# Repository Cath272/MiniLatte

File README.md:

# MiniLatte

## Introduction
MiniLatte is a Mini Pc made using the LattePanda Mu compute module

## General description
The device is a x86 desktop comuter with lots of IO ports like USB, PCIe, Ethernet and more. 

## Problems
Esp32 and GL3224 do not enumerate sometimes
The headphone jack is not correctly wired and i did not figure out how to fix it yet

### Block diagram

## Hardware Design
### LattePanda Mu 
The LattePanda Mu is a compute module with rich IO with up to 9 PCIe slots, lots of usb, gpio and much more.
The module is Avaliable with 8 or 16gb of LPDDR5 ram, and an Intel N100 or Intel N305 CPU, the module uses a SODIMM DDR4 slot to connect to the carrier pcb

## ICs 
The board uses a lot of ics, so to avoid a long section about ics you can find the complete list of ICs in an the BOM generator in KiCad
All parts that are not generic (Like caps and resistors) are directly imported from LCSC so they also have an LCSC id 
Please read the warning on the IT8851-128 if you want to build the board.

Some of the chips are not available on components sourcing sites like DigiKey or LCSC but can be easliy found of Aliexpress.
Some notable Ics used by the board:

### VL822-Q7
USB 3.2 Gen 2 USB Hub 10Gbps with 4 downstream ports, used to increase the number of usb from 2 to 8

### GL3224ONY
USB 3.2 Gen 1 to dual Sd card controller, used to have 2 sd cards slots on the pcb

### IT8851FN-128
Usb Type C DP alt mode Controller, used for having a usb C port with Displayport output, the chip is a bit hard to get but you can find it on Aliexpress if you ask some BOM sellers. The chip also needs to be flashed so ask the Lattepanda team for the flashing firmware.
The chip variant needs to be "IT8851-128" EXACTLY, other variants do not work.  

### TPS51275

Main Power Ic, used for DC-DC from 20v to 3.3v and 5v

### VL162
USB Type-C 2:4 differential channels mux switch and integrated CC logic function for USB 3.1 type-C application. Needed for the type C ports to work both ways.

### RTL8125BG
PCIe to 2.5Gbps Ethernet controller

## Schematic
[Schematic](PCB/MiniLatte.pdf)

## PCB

## LED Array

The board connects to a secoundary board that an WS2812C LED Array made out of 220 leds (5x44). The Controller for the LEDs is on the main pcb and it is a ESP32 C3

## Case and 3d design

The case was make using AutoCad and exported to stl
The stl files can be found in the 3D Models folder.
The case is made of 2 parts and there is a diffusion layer for the LED PCB

## Bachlors Degree
This project was made as a project for my bachlor's degree, you can find the thesis and a shorts powerpoint in the "lucrare licenta" folder but it is in romanian. It provides some details of the building process of this pcb. You can also find some extra pics in the same folder.

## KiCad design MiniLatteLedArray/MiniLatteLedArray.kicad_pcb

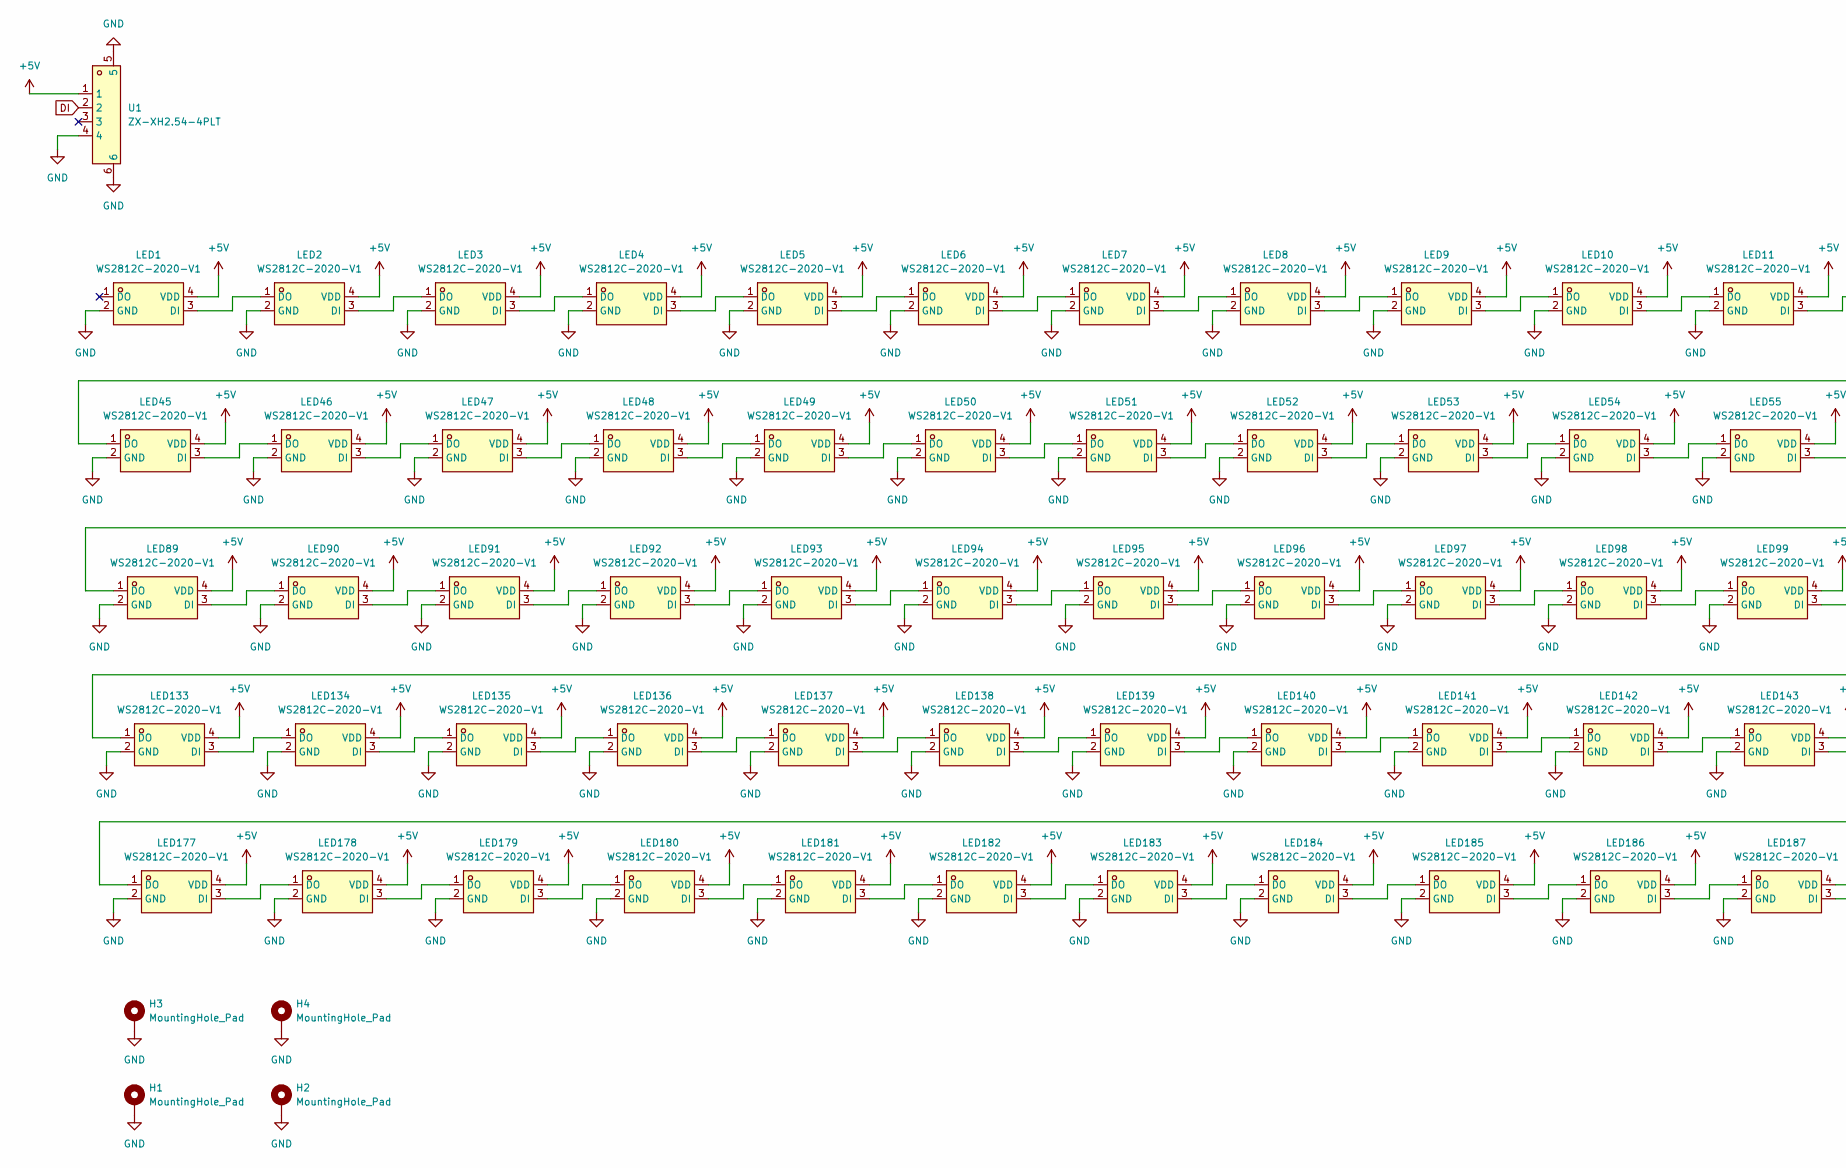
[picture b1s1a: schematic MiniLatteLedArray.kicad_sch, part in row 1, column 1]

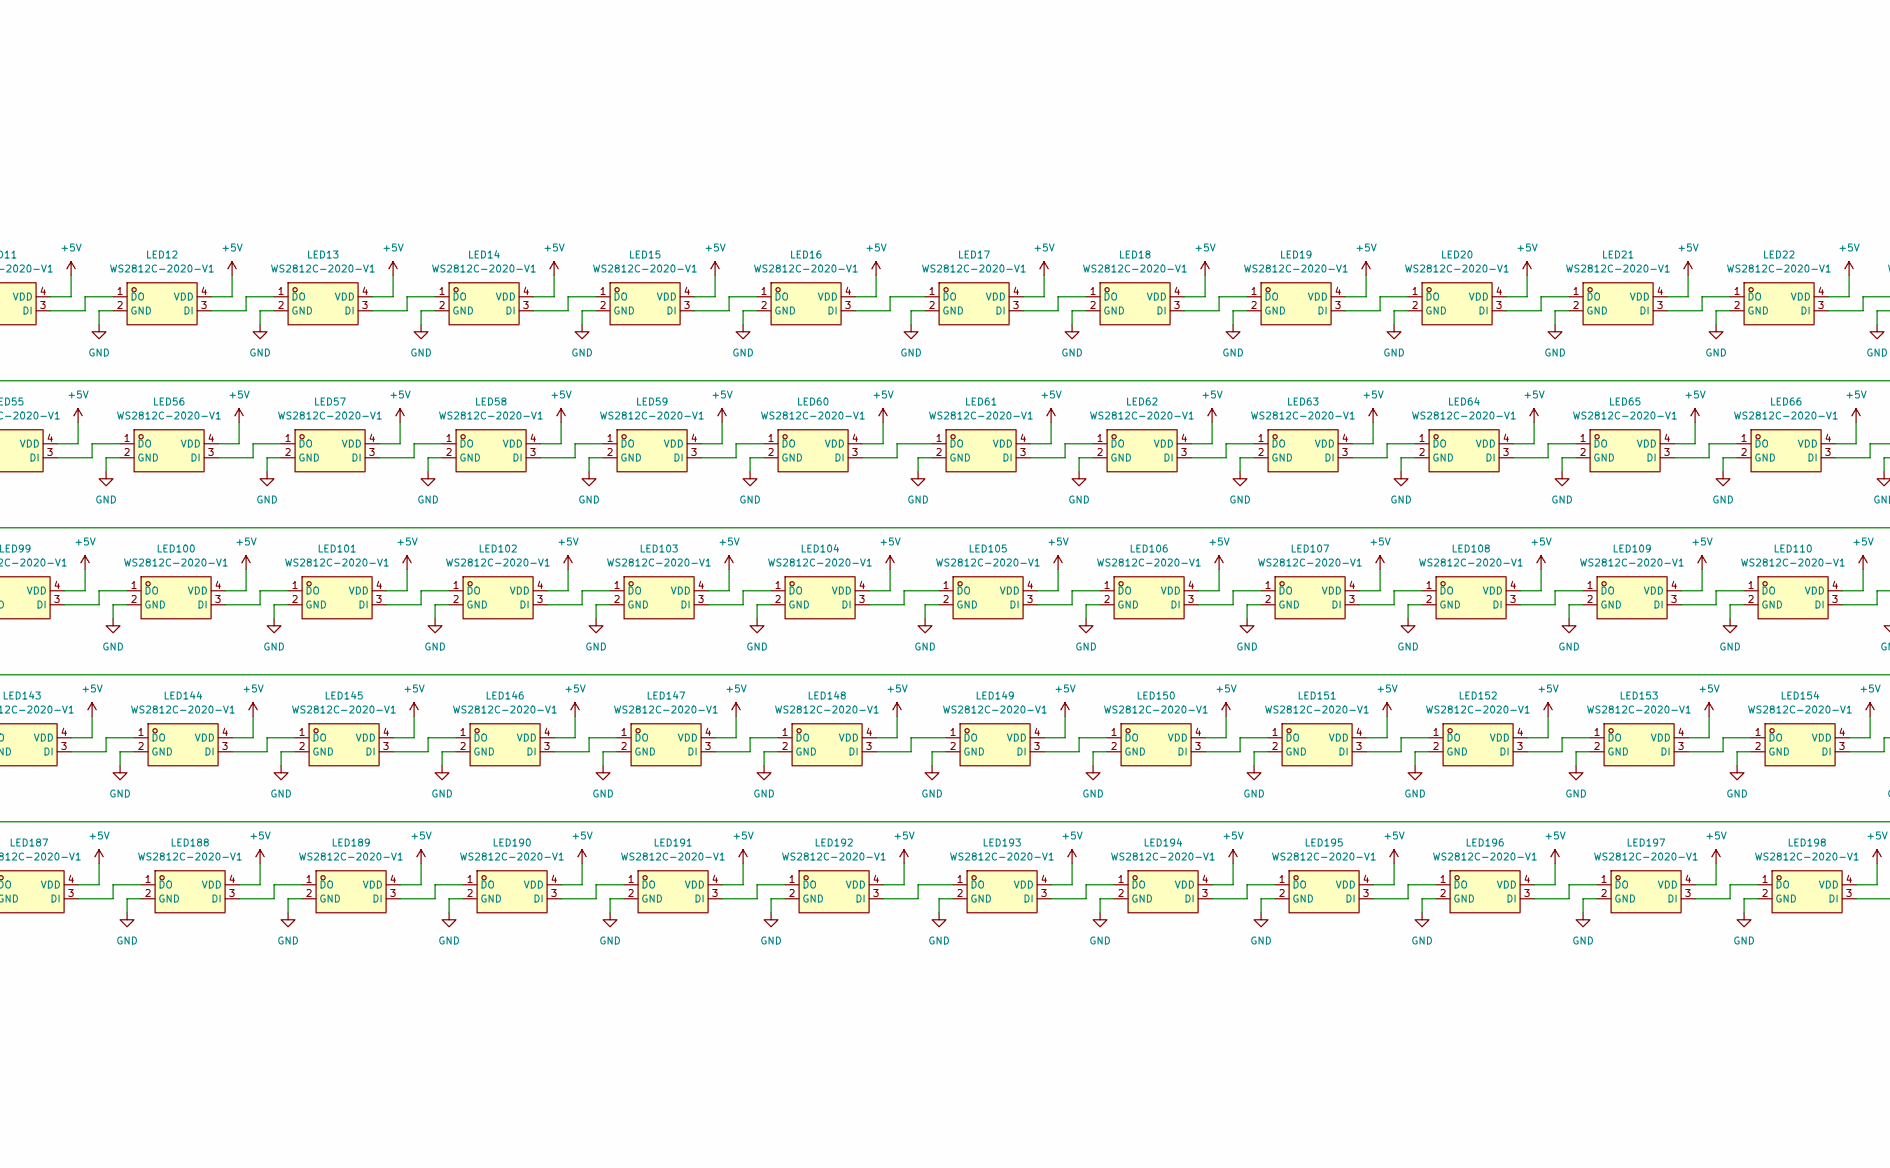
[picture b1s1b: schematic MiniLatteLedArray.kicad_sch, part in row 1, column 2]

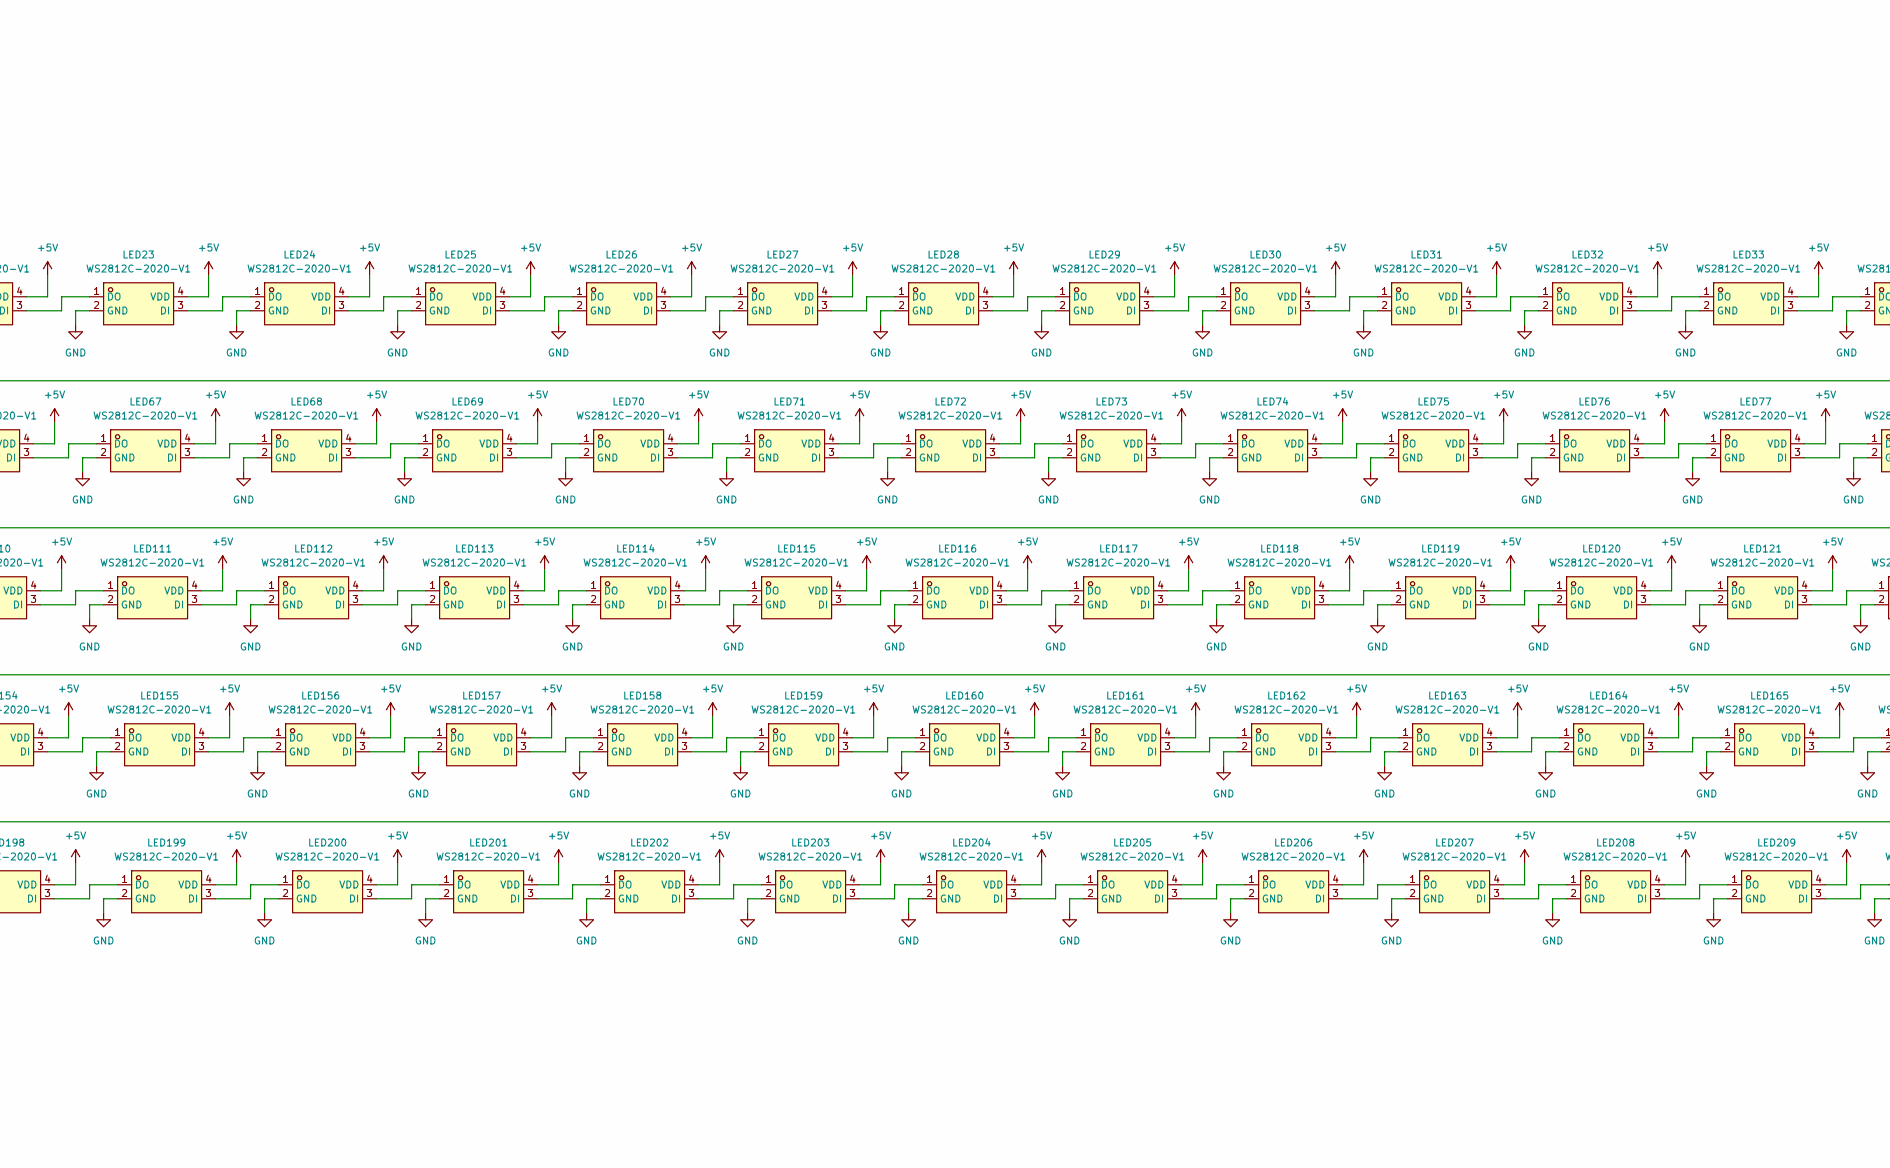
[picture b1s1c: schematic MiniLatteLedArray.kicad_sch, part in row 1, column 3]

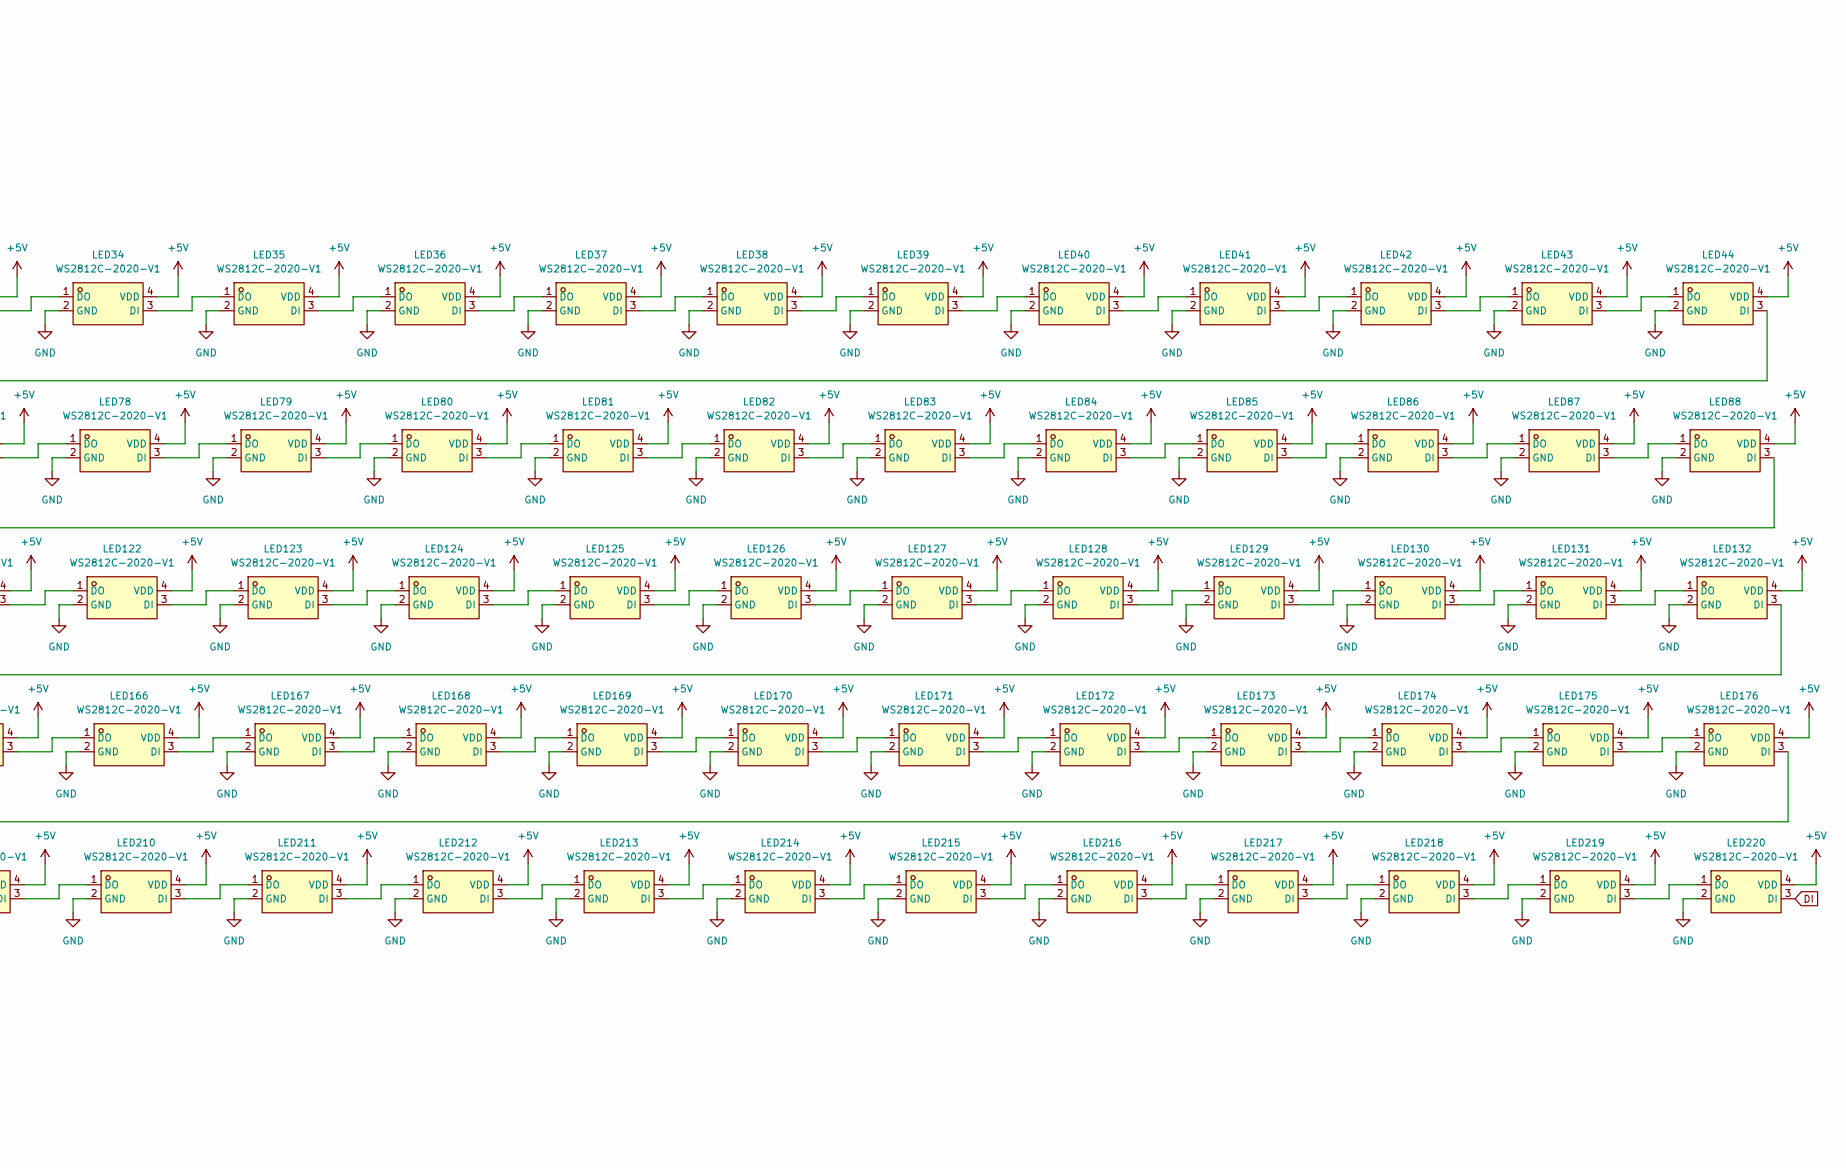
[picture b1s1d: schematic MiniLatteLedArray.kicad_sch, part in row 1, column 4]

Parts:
H1, H2, H3, H4: MountingHole_Pad; MountingHole_2.2mm_M2_DIN965_Pad_TopOnly
LED1, LED2, LED3, LED4, LED5, LED6, LED7, LED8, LED9, LED10, LED11, LED12, LED13, LED14, LED15, LED16, LED17, LED18, LED19, LED20, LED21, LED22, LED23, LED24, LED25, LED26, LED27, LED28, LED29, LED30, LED31, LED32, LED33, LED34, LED35, LED36, LED37, LED38, LED39, LED40, LED41, LED42, LED43, LED44, LED45, LED46, LED47, LED48, LED49, LED50, LED51, LED52, LED53, LED54, LED55, LED56, LED57, LED58, LED59, LED60, LED61, LED62, LED63, LED64, LED65, LED66, LED67, LED68, LED69, LED70, LED71, LED72, LED73, LED74, LED75, LED76, LED77, LED78, LED79, LED80, LED81, LED82, LED83, LED84, LED85, LED86, LED87, LED88, LED89, LED90, LED91, LED92, LED93, LED94, LED95, LED96, LED97, LED98, LED99, LED100, LED101, LED102, LED103, LED104, LED105, LED106, LED107, LED108, LED109, LED110, LED111, LED112, LED113, LED114, LED115, LED116, LED117, LED118, LED119, LED120, LED121, LED122, LED123, LED124, LED125, LED126, LED127, LED128, LED129, LED130, LED131, LED132, LED133, LED134, LED135, LED136, LED137, LED138, LED139, LED140, LED141, LED142, LED143, LED144, LED145, LED146, LED147, LED148, LED149, LED150, LED151, LED152, LED153, LED154, LED155, LED156, LED157, LED158, LED159, LED160, LED161, LED162, LED163, LED164, LED165, LED166, LED167, LED168, LED169, LED170, LED171, LED172, LED173, LED174, LED175, LED176, LED177, LED178, LED179, LED180, LED181, LED182, LED183, LED184, LED185, LED186, LED187, LED188, LED189, LED190, LED191, LED192, LED193, LED194, LED195, LED196, LED197, LED198, LED199, LED200, LED201, LED202, LED203, LED204, LED205, LED206, LED207, LED208, LED209, LED210, LED211, LED212, LED213, LED214, LED215, LED216, LED217, LED218, LED219, LED220: WS2812C-2020-V1; LED-SMD_4P-L2.0-W2.0-TL_WS2812B-2020; LCSC Part C2976072
U1: ZX-XH2.54-4PLT; CONN-SMD_4P-P2.54_C9900012758; LCSC Part C7429682

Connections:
+5V: LED1.4 (VDD), LED2.4 (VDD), LED3.4 (VDD), LED4.4 (VDD), LED5.4 (VDD), LED6.4 (VDD), LED7.4 (VDD), LED8.4 (VDD), LED9.4 (VDD), LED10.4 (VDD), LED11.4 (VDD), LED12.4 (VDD), LED13.4 (VDD), LED14.4 (VDD), LED15.4 (VDD), LED16.4 (VDD), LED17.4 (VDD), LED18.4 (VDD), LED19.4 (VDD), LED20.4 (VDD), LED21.4 (VDD), LED22.4 (VDD), LED23.4 (VDD), LED24.4 (VDD), LED25.4 (VDD), LED26.4 (VDD), LED27.4 (VDD), LED28.4 (VDD), LED29.4 (VDD), LED30.4 (VDD), LED31.4 (VDD), LED32.4 (VDD), LED33.4 (VDD), LED34.4 (VDD), LED35.4 (VDD), LED36.4 (VDD), LED37.4 (VDD), LED38.4 (VDD), LED39.4 (VDD), LED40.4 (VDD), LED41.4 (VDD), LED42.4 (VDD), LED43.4 (VDD), LED44.4 (VDD), LED45.4 (VDD), LED46.4 (VDD), LED47.4 (VDD), LED48.4 (VDD), LED49.4 (VDD), LED50.4 (VDD), LED51.4 (VDD), LED52.4 (VDD), LED53.4 (VDD), LED54.4 (VDD), LED55.4 (VDD), LED56.4 (VDD), LED57.4 (VDD), LED58.4 (VDD), LED59.4 (VDD), LED60.4 (VDD), LED61.4 (VDD), LED62.4 (VDD), LED63.4 (VDD), LED64.4 (VDD), LED65.4 (VDD), LED66.4 (VDD), LED67.4 (VDD), LED68.4 (VDD), LED69.4 (VDD), LED70.4 (VDD), LED71.4 (VDD), LED72.4 (VDD), LED73.4 (VDD), LED74.4 (VDD), LED75.4 (VDD), LED76.4 (VDD), LED77.4 (VDD), LED78.4 (VDD), LED79.4 (VDD), LED80.4 (VDD), LED81.4 (VDD), LED82.4 (VDD), LED83.4 (VDD), LED84.4 (VDD), LED85.4 (VDD), LED86.4 (VDD), LED87.4 (VDD), LED88.4 (VDD), LED89.4 (VDD), LED90.4 (VDD), LED91.4 (VDD), LED92.4 (VDD), LED93.4 (VDD), LED94.4 (VDD), LED95.4 (VDD), LED96.4 (VDD), LED97.4 (VDD), LED98.4 (VDD), LED99.4 (VDD), LED100.4 (VDD), LED101.4 (VDD), LED102.4 (VDD), LED103.4 (VDD), LED104.4 (VDD), LED105.4 (VDD), LED106.4 (VDD), LED107.4 (VDD), LED108.4 (VDD), LED109.4 (VDD), LED110.4 (VDD), LED111.4 (VDD), LED112.4 (VDD), LED113.4 (VDD), LED114.4 (VDD), LED115.4 (VDD), LED116.4 (VDD), LED117.4 (VDD), LED118.4 (VDD), LED119.4 (VDD), LED120.4 (VDD), LED121.4 (VDD), LED122.4 (VDD), LED123.4 (VDD), LED124.4 (VDD), LED125.4 (VDD), LED126.4 (VDD), LED127.4 (VDD), LED128.4 (VDD), LED129.4 (VDD), LED130.4 (VDD), LED131.4 (VDD), LED132.4 (VDD), LED133.4 (VDD), LED134.4 (VDD), LED135.4 (VDD), LED136.4 (VDD), LED137.4 (VDD), LED138.4 (VDD), LED139.4 (VDD), LED140.4 (VDD), LED141.4 (VDD), LED142.4 (VDD), LED143.4 (VDD), LED144.4 (VDD), LED145.4 (VDD), LED146.4 (VDD), LED147.4 (VDD), LED148.4 (VDD), LED149.4 (VDD), LED150.4 (VDD), LED151.4 (VDD), LED152.4 (VDD), LED153.4 (VDD), LED154.4 (VDD), LED155.4 (VDD), LED156.4 (VDD), LED157.4 (VDD), LED158.4 (VDD), LED159.4 (VDD), LED160.4 (VDD), LED161.4 (VDD), LED162.4 (VDD), LED163.4 (VDD), LED164.4 (VDD), LED165.4 (VDD), LED166.4 (VDD), LED167.4 (VDD), LED168.4 (VDD), LED169.4 (VDD), LED170.4 (VDD), LED171.4 (VDD), LED172.4 (VDD), LED173.4 (VDD), LED174.4 (VDD), LED175.4 (VDD), LED176.4 (VDD), LED177.4 (VDD), LED178.4 (VDD), LED179.4 (VDD), LED180.4 (VDD), LED181.4 (VDD), LED182.4 (VDD), LED183.4 (VDD), LED184.4 (VDD), LED185.4 (VDD), LED186.4 (VDD), LED187.4 (VDD), LED188.4 (VDD), LED189.4 (VDD), LED190.4 (VDD), LED191.4 (VDD), LED192.4 (VDD), LED193.4 (VDD), LED194.4 (VDD), LED195.4 (VDD), LED196.4 (VDD), LED197.4 (VDD), LED198.4 (VDD), LED199.4 (VDD), LED200.4 (VDD), LED201.4 (VDD), LED202.4 (VDD), LED203.4 (VDD), LED204.4 (VDD), LED205.4 (VDD), LED206.4 (VDD), LED207.4 (VDD), LED208.4 (VDD), LED209.4 (VDD), LED210.4 (VDD), LED211.4 (VDD), LED212.4 (VDD), LED213.4 (VDD), LED214.4 (VDD), LED215.4 (VDD), LED216.4 (VDD), LED217.4 (VDD), LED218.4 (VDD), LED219.4 (VDD), LED220.4 (VDD), U1.1
DI: LED220.3 (DI), U1.2
GND: H1.1, H2.1, H3.1, H4.1, LED1.2 (GND), LED2.2 (GND), LED3.2 (GND), LED4.2 (GND), LED5.2 (GND), LED6.2 (GND), LED7.2 (GND), LED8.2 (GND), LED9.2 (GND), LED10.2 (GND), LED11.2 (GND), LED12.2 (GND), LED13.2 (GND), LED14.2 (GND), LED15.2 (GND), LED16.2 (GND), LED17.2 (GND), LED18.2 (GND), LED19.2 (GND), LED20.2 (GND), LED21.2 (GND), LED22.2 (GND), LED23.2 (GND), LED24.2 (GND), LED25.2 (GND), LED26.2 (GND), LED27.2 (GND), LED28.2 (GND), LED29.2 (GND), LED30.2 (GND), LED31.2 (GND), LED32.2 (GND), LED33.2 (GND), LED34.2 (GND), LED35.2 (GND), LED36.2 (GND), LED37.2 (GND), LED38.2 (GND), LED39.2 (GND), LED40.2 (GND), LED41.2 (GND), LED42.2 (GND), LED43.2 (GND), LED44.2 (GND), LED45.2 (GND), LED46.2 (GND), LED47.2 (GND), LED48.2 (GND), LED49.2 (GND), LED50.2 (GND), LED51.2 (GND), LED52.2 (GND), LED53.2 (GND), LED54.2 (GND), LED55.2 (GND), LED56.2 (GND), LED57.2 (GND), LED58.2 (GND), LED59.2 (GND), LED60.2 (GND), LED61.2 (GND), LED62.2 (GND), LED63.2 (GND), LED64.2 (GND), LED65.2 (GND), LED66.2 (GND), LED67.2 (GND), LED68.2 (GND), LED69.2 (GND), LED70.2 (GND), LED71.2 (GND), LED72.2 (GND), LED73.2 (GND), LED74.2 (GND), LED75.2 (GND), LED76.2 (GND), LED77.2 (GND), LED78.2 (GND), LED79.2 (GND), LED80.2 (GND), LED81.2 (GND), LED82.2 (GND), LED83.2 (GND), LED84.2 (GND), LED85.2 (GND), LED86.2 (GND), LED87.2 (GND), LED88.2 (GND), LED89.2 (GND), LED90.2 (GND), LED91.2 (GND), LED92.2 (GND), LED93.2 (GND), LED94.2 (GND), LED95.2 (GND), LED96.2 (GND), LED97.2 (GND), LED98.2 (GND), LED99.2 (GND), LED100.2 (GND), LED101.2 (GND), LED102.2 (GND), LED103.2 (GND), LED104.2 (GND), LED105.2 (GND), LED106.2 (GND), LED107.2 (GND), LED108.2 (GND), LED109.2 (GND), LED110.2 (GND), LED111.2 (GND), LED112.2 (GND), LED113.2 (GND), LED114.2 (GND), LED115.2 (GND), LED116.2 (GND), LED117.2 (GND), LED118.2 (GND), LED119.2 (GND), LED120.2 (GND), LED121.2 (GND), LED122.2 (GND), LED123.2 (GND), LED124.2 (GND), LED125.2 (GND), LED126.2 (GND), LED127.2 (GND), LED128.2 (GND), LED129.2 (GND), LED130.2 (GND), LED131.2 (GND), LED132.2 (GND), LED133.2 (GND), LED134.2 (GND), LED135.2 (GND), LED136.2 (GND), LED137.2 (GND), LED138.2 (GND), LED139.2 (GND), LED140.2 (GND), LED141.2 (GND), LED142.2 (GND), LED143.2 (GND), LED144.2 (GND), LED145.2 (GND), LED146.2 (GND), LED147.2 (GND), LED148.2 (GND), LED149.2 (GND), LED150.2 (GND), LED151.2 (GND), LED152.2 (GND), LED153.2 (GND), LED154.2 (GND), LED155.2 (GND), LED156.2 (GND), LED157.2 (GND), LED158.2 (GND), LED159.2 (GND), LED160.2 (GND), LED161.2 (GND), LED162.2 (GND), LED163.2 (GND), LED164.2 (GND), LED165.2 (GND), LED166.2 (GND), LED167.2 (GND), LED168.2 (GND), LED169.2 (GND), LED170.2 (GND), LED171.2 (GND), LED172.2 (GND), LED173.2 (GND), LED174.2 (GND), LED175.2 (GND), LED176.2 (GND), LED177.2 (GND), LED178.2 (GND), LED179.2 (GND), LED180.2 (GND), LED181.2 (GND), LED182.2 (GND), LED183.2 (GND), LED184.2 (GND), LED185.2 (GND), LED186.2 (GND), LED187.2 (GND), LED188.2 (GND), LED189.2 (GND), LED190.2 (GND), LED191.2 (GND), LED192.2 (GND), LED193.2 (GND), LED194.2 (GND), LED195.2 (GND), LED196.2 (GND), LED197.2 (GND), LED198.2 (GND), LED199.2 (GND), LED200.2 (GND), LED201.2 (GND), LED202.2 (GND), LED203.2 (GND), LED204.2 (GND), LED205.2 (GND), LED206.2 (GND), LED207.2 (GND), LED208.2 (GND), LED209.2 (GND), LED210.2 (GND), LED211.2 (GND), LED212.2 (GND), LED213.2 (GND), LED214.2 (GND), LED215.2 (GND), LED216.2 (GND), LED217.2 (GND), LED218.2 (GND), LED219.2 (GND), LED220.2 (GND), U1.4, U1.5, U1.6
unnamed: LED1.3 (DI), LED2.1 (DO)
unnamed: LED2.3 (DI), LED3.1 (DO)
unnamed: LED3.3 (DI), LED4.1 (DO)
unnamed: LED4.3 (DI), LED5.1 (DO)
unnamed: LED5.3 (DI), LED6.1 (DO)
unnamed: LED6.3 (DI), LED7.1 (DO)
unnamed: LED7.3 (DI), LED8.1 (DO)
unnamed: LED8.3 (DI), LED9.1 (DO)
unnamed: LED10.3 (DI), LED11.1 (DO)
unnamed: LED9.3 (DI), LED10.1 (DO)
unnamed: LED11.3 (DI), LED12.1 (DO)
unnamed: LED12.3 (DI), LED13.1 (DO)
unnamed: LED13.3 (DI), LED14.1 (DO)
unnamed: LED14.3 (DI), LED15.1 (DO)
unnamed: LED15.3 (DI), LED16.1 (DO)
unnamed: LED16.3 (DI), LED17.1 (DO)
unnamed: LED17.3 (DI), LED18.1 (DO)
unnamed: LED18.3 (DI), LED19.1 (DO)
unnamed: LED19.3 (DI), LED20.1 (DO)
unnamed: LED20.3 (DI), LED21.1 (DO)
unnamed: LED21.3 (DI), LED22.1 (DO)
unnamed: LED22.3 (DI), LED23.1 (DO)
unnamed: LED23.3 (DI), LED24.1 (DO)
unnamed: LED24.3 (DI), LED25.1 (DO)
unnamed: LED25.3 (DI), LED26.1 (DO)
unnamed: LED26.3 (DI), LED27.1 (DO)
unnamed: LED27.3 (DI), LED28.1 (DO)
unnamed: LED28.3 (DI), LED29.1 (DO)
unnamed: LED29.3 (DI), LED30.1 (DO)
unnamed: LED30.3 (DI), LED31.1 (DO)
unnamed: LED31.3 (DI), LED32.1 (DO)
unnamed: LED32.3 (DI), LED33.1 (DO)
unnamed: LED33.3 (DI), LED34.1 (DO)
unnamed: LED34.3 (DI), LED35.1 (DO)
unnamed: LED35.3 (DI), LED36.1 (DO)
unnamed: LED36.3 (DI), LED37.1 (DO)
unnamed: LED37.3 (DI), LED38.1 (DO)
unnamed: LED38.3 (DI), LED39.1 (DO)
unnamed: LED39.3 (DI), LED40.1 (DO)
unnamed: LED40.3 (DI), LED41.1 (DO)
unnamed: LED41.3 (DI), LED42.1 (DO)
unnamed: LED42.3 (DI), LED43.1 (DO)
unnamed: LED43.3 (DI), LED44.1 (DO)
unnamed: LED44.3 (DI), LED45.1 (DO)
unnamed: LED45.3 (DI), LED46.1 (DO)
unnamed: LED46.3 (DI), LED47.1 (DO)
unnamed: LED47.3 (DI), LED48.1 (DO)
unnamed: LED48.3 (DI), LED49.1 (DO)
unnamed: LED49.3 (DI), LED50.1 (DO)
unnamed: LED50.3 (DI), LED51.1 (DO)
unnamed: LED51.3 (DI), LED52.1 (DO)
unnamed: LED52.3 (DI), LED53.1 (DO)
unnamed: LED53.3 (DI), LED54.1 (DO)
unnamed: LED54.3 (DI), LED55.1 (DO)
unnamed: LED55.3 (DI), LED56.1 (DO)
unnamed: LED56.3 (DI), LED57.1 (DO)
unnamed: LED57.3 (DI), LED58.1 (DO)
unnamed: LED58.3 (DI), LED59.1 (DO)
unnamed: LED59.3 (DI), LED60.1 (DO)
unnamed: LED60.3 (DI), LED61.1 (DO)
unnamed: LED61.3 (DI), LED62.1 (DO)
unnamed: LED62.3 (DI), LED63.1 (DO)
unnamed: LED63.3 (DI), LED64.1 (DO)
unnamed: LED64.3 (DI), LED65.1 (DO)
unnamed: LED65.3 (DI), LED66.1 (DO)
unnamed: LED66.3 (DI), LED67.1 (DO)
unnamed: LED67.3 (DI), LED68.1 (DO)
unnamed: LED68.3 (DI), LED69.1 (DO)
unnamed: LED69.3 (DI), LED70.1 (DO)
unnamed: LED70.3 (DI), LED71.1 (DO)
unnamed: LED71.3 (DI), LED72.1 (DO)
unnamed: LED72.3 (DI), LED73.1 (DO)
unnamed: LED73.3 (DI), LED74.1 (DO)
unnamed: LED74.3 (DI), LED75.1 (DO)
unnamed: LED75.3 (DI), LED76.1 (DO)
unnamed: LED76.3 (DI), LED77.1 (DO)
unnamed: LED77.3 (DI), LED78.1 (DO)
unnamed: LED78.3 (DI), LED79.1 (DO)
unnamed: LED79.3 (DI), LED80.1 (DO)
unnamed: LED80.3 (DI), LED81.1 (DO)
unnamed: LED81.3 (DI), LED82.1 (DO)
unnamed: LED82.3 (DI), LED83.1 (DO)
unnamed: LED83.3 (DI), LED84.1 (DO)
unnamed: LED84.3 (DI), LED85.1 (DO)
unnamed: LED85.3 (DI), LED86.1 (DO)
unnamed: LED86.3 (DI), LED87.1 (DO)
unnamed: LED87.3 (DI), LED88.1 (DO)
unnamed: LED88.3 (DI), LED89.1 (DO)
unnamed: LED89.3 (DI), LED90.1 (DO)
unnamed: LED90.3 (DI), LED91.1 (DO)
unnamed: LED91.3 (DI), LED92.1 (DO)
unnamed: LED92.3 (DI), LED93.1 (DO)
unnamed: LED93.3 (DI), LED94.1 (DO)
unnamed: LED94.3 (DI), LED95.1 (DO)
unnamed: LED95.3 (DI), LED96.1 (DO)
unnamed: LED96.3 (DI), LED97.1 (DO)
unnamed: LED97.3 (DI), LED98.1 (DO)
unnamed: LED98.3 (DI), LED99.1 (DO)
unnamed: LED100.3 (DI), LED101.1 (DO)
unnamed: LED99.3 (DI), LED100.1 (DO)
unnamed: LED101.3 (DI), LED102.1 (DO)
unnamed: LED102.3 (DI), LED103.1 (DO)
unnamed: LED103.3 (DI), LED104.1 (DO)
unnamed: LED104.3 (DI), LED105.1 (DO)
unnamed: LED105.3 (DI), LED106.1 (DO)
unnamed: LED106.3 (DI), LED107.1 (DO)
unnamed: LED107.3 (DI), LED108.1 (DO)
unnamed: LED108.3 (DI), LED109.1 (DO)
unnamed: LED109.3 (DI), LED110.1 (DO)
unnamed: LED110.3 (DI), LED111.1 (DO)
unnamed: LED111.3 (DI), LED112.1 (DO)
unnamed: LED112.3 (DI), LED113.1 (DO)
unnamed: LED113.3 (DI), LED114.1 (DO)
unnamed: LED114.3 (DI), LED115.1 (DO)
unnamed: LED115.3 (DI), LED116.1 (DO)
unnamed: LED116.3 (DI), LED117.1 (DO)
unnamed: LED117.3 (DI), LED118.1 (DO)
unnamed: LED118.3 (DI), LED119.1 (DO)
unnamed: LED119.3 (DI), LED120.1 (DO)
unnamed: LED120.3 (DI), LED121.1 (DO)
unnamed: LED121.3 (DI), LED122.1 (DO)
unnamed: LED122.3 (DI), LED123.1 (DO)
unnamed: LED123.3 (DI), LED124.1 (DO)
unnamed: LED124.3 (DI), LED125.1 (DO)
unnamed: LED125.3 (DI), LED126.1 (DO)
unnamed: LED126.3 (DI), LED127.1 (DO)
unnamed: LED127.3 (DI), LED128.1 (DO)
unnamed: LED128.3 (DI), LED129.1 (DO)
unnamed: LED129.3 (DI), LED130.1 (DO)
unnamed: LED130.3 (DI), LED131.1 (DO)
unnamed: LED131.3 (DI), LED132.1 (DO)
unnamed: LED132.3 (DI), LED133.1 (DO)
unnamed: LED133.3 (DI), LED134.1 (DO)
unnamed: LED134.3 (DI), LED135.1 (DO)
unnamed: LED135.3 (DI), LED136.1 (DO)
unnamed: LED136.3 (DI), LED137.1 (DO)
unnamed: LED137.3 (DI), LED138.1 (DO)
unnamed: LED138.3 (DI), LED139.1 (DO)
unnamed: LED139.3 (DI), LED140.1 (DO)
unnamed: LED140.3 (DI), LED141.1 (DO)
unnamed: LED141.3 (DI), LED142.1 (DO)
unnamed: LED142.3 (DI), LED143.1 (DO)
unnamed: LED143.3 (DI), LED144.1 (DO)
unnamed: LED144.3 (DI), LED145.1 (DO)
unnamed: LED145.3 (DI), LED146.1 (DO)
unnamed: LED146.3 (DI), LED147.1 (DO)
unnamed: LED147.3 (DI), LED148.1 (DO)
unnamed: LED148.3 (DI), LED149.1 (DO)
unnamed: LED149.3 (DI), LED150.1 (DO)
unnamed: LED150.3 (DI), LED151.1 (DO)
unnamed: LED151.3 (DI), LED152.1 (DO)
unnamed: LED152.3 (DI), LED153.1 (DO)
unnamed: LED153.3 (DI), LED154.1 (DO)
unnamed: LED154.3 (DI), LED155.1 (DO)
unnamed: LED155.3 (DI), LED156.1 (DO)
unnamed: LED156.3 (DI), LED157.1 (DO)
unnamed: LED157.3 (DI), LED158.1 (DO)
unnamed: LED158.3 (DI), LED159.1 (DO)
unnamed: LED159.3 (DI), LED160.1 (DO)
unnamed: LED160.3 (DI), LED161.1 (DO)
unnamed: LED161.3 (DI), LED162.1 (DO)
unnamed: LED162.3 (DI), LED163.1 (DO)
unnamed: LED163.3 (DI), LED164.1 (DO)
unnamed: LED164.3 (DI), LED165.1 (DO)
unnamed: LED165.3 (DI), LED166.1 (DO)
unnamed: LED166.3 (DI), LED167.1 (DO)
unnamed: LED167.3 (DI), LED168.1 (DO)
unnamed: LED168.3 (DI), LED169.1 (DO)
unnamed: LED169.3 (DI), LED170.1 (DO)
unnamed: LED170.3 (DI), LED171.1 (DO)
unnamed: LED171.3 (DI), LED172.1 (DO)
unnamed: LED172.3 (DI), LED173.1 (DO)
unnamed: LED173.3 (DI), LED174.1 (DO)
unnamed: LED174.3 (DI), LED175.1 (DO)
unnamed: LED175.3 (DI), LED176.1 (DO)
unnamed: LED176.3 (DI), LED177.1 (DO)
unnamed: LED177.3 (DI), LED178.1 (DO)
unnamed: LED178.3 (DI), LED179.1 (DO)
unnamed: LED179.3 (DI), LED180.1 (DO)
unnamed: LED180.3 (DI), LED181.1 (DO)
unnamed: LED181.3 (DI), LED182.1 (DO)
unnamed: LED182.3 (DI), LED183.1 (DO)
unnamed: LED183.3 (DI), LED184.1 (DO)
unnamed: LED184.3 (DI), LED185.1 (DO)
unnamed: LED185.3 (DI), LED186.1 (DO)
unnamed: LED186.3 (DI), LED187.1 (DO)
unnamed: LED187.3 (DI), LED188.1 (DO)
unnamed: LED188.3 (DI), LED189.1 (DO)
unnamed: LED189.3 (DI), LED190.1 (DO)
unnamed: LED190.3 (DI), LED191.1 (DO)
unnamed: LED191.3 (DI), LED192.1 (DO)
unnamed: LED192.3 (DI), LED193.1 (DO)
unnamed: LED193.3 (DI), LED194.1 (DO)
unnamed: LED194.3 (DI), LED195.1 (DO)
unnamed: LED195.3 (DI), LED196.1 (DO)
unnamed: LED196.3 (DI), LED197.1 (DO)
unnamed: LED197.3 (DI), LED198.1 (DO)
unnamed: LED198.3 (DI), LED199.1 (DO)
unnamed: LED199.3 (DI), LED200.1 (DO)
unnamed: LED200.3 (DI), LED201.1 (DO)
unnamed: LED201.3 (DI), LED202.1 (DO)
unnamed: LED202.3 (DI), LED203.1 (DO)
unnamed: LED203.3 (DI), LED204.1 (DO)
unnamed: LED204.3 (DI), LED205.1 (DO)
unnamed: LED205.3 (DI), LED206.1 (DO)
unnamed: LED206.3 (DI), LED207.1 (DO)
unnamed: LED207.3 (DI), LED208.1 (DO)
unnamed: LED208.3 (DI), LED209.1 (DO)
unnamed: LED209.3 (DI), LED210.1 (DO)
unnamed: LED210.3 (DI), LED211.1 (DO)
unnamed: LED211.3 (DI), LED212.1 (DO)
unnamed: LED212.3 (DI), LED213.1 (DO)
unnamed: LED213.3 (DI), LED214.1 (DO)
unnamed: LED214.3 (DI), LED215.1 (DO)
unnamed: LED215.3 (DI), LED216.1 (DO)
unnamed: LED216.3 (DI), LED217.1 (DO)
unnamed: LED217.3 (DI), LED218.1 (DO)
unnamed: LED218.3 (DI), LED219.1 (DO)
unnamed: LED219.3 (DI), LED220.1 (DO)

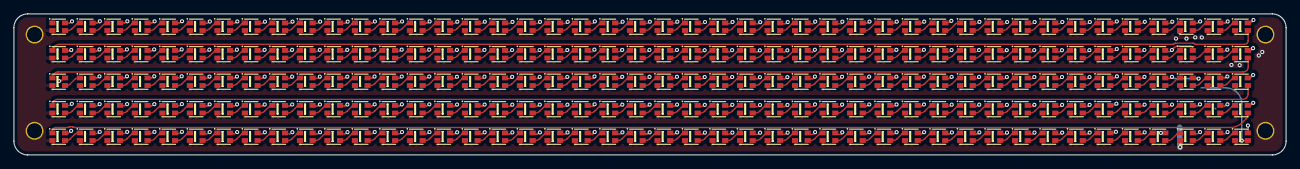
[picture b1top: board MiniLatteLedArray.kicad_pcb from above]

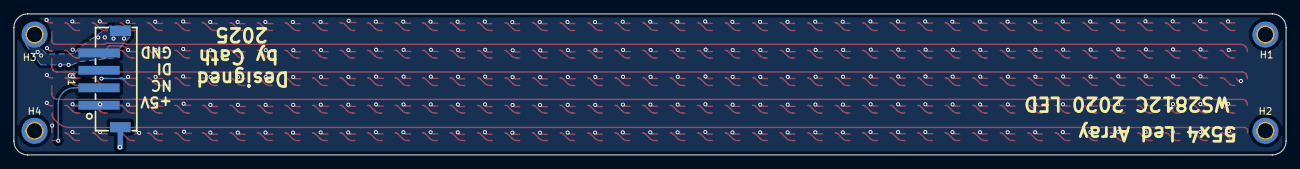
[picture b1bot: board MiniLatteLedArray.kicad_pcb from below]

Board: 2 copper layers, 185.0 x 20.5 mm, 225 parts (5 on the bottom side), 222 nets.
